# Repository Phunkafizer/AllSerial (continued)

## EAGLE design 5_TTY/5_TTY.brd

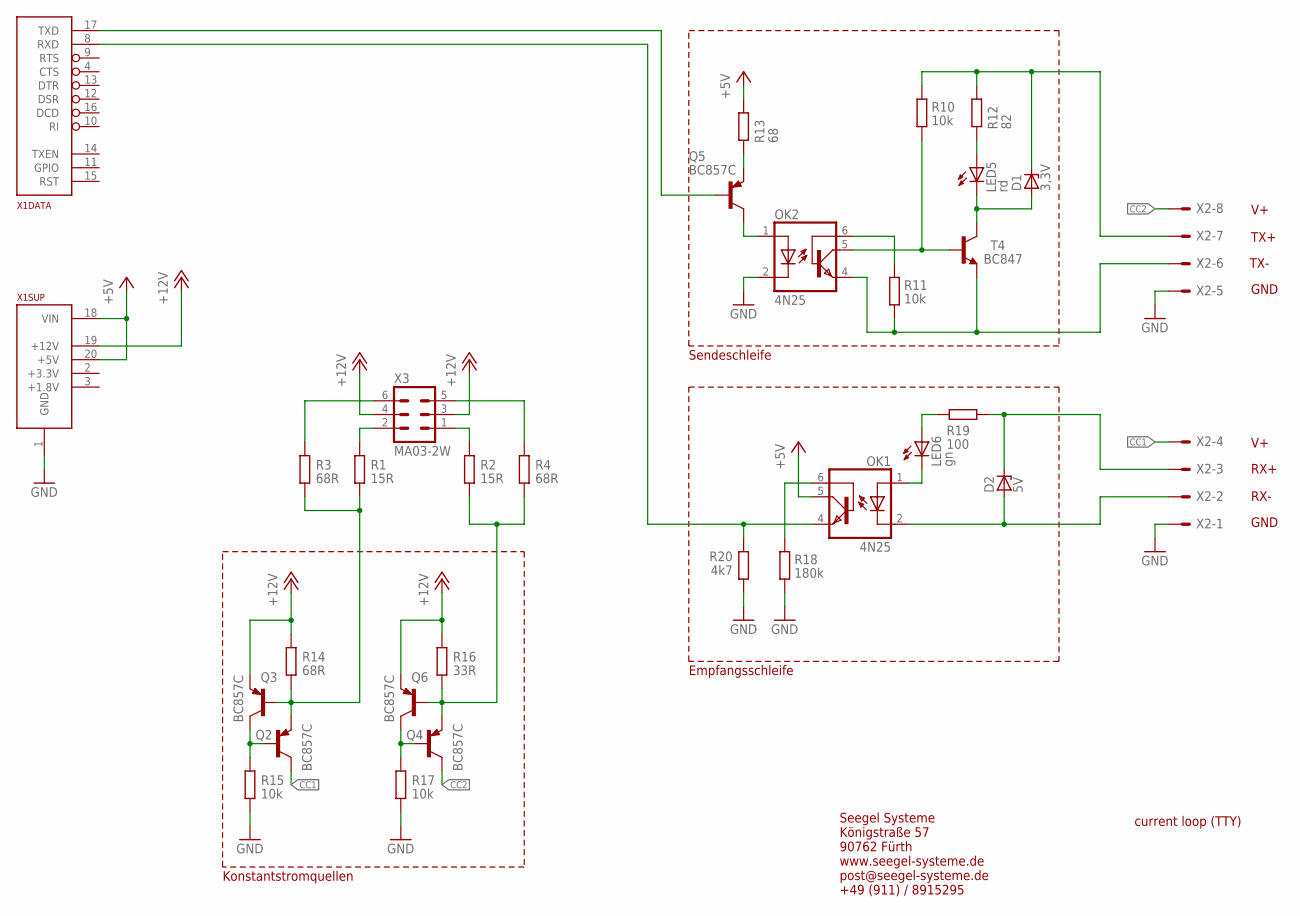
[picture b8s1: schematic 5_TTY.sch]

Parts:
D1: 3,3V; SOT23
D2: 5V; SOT23
LED5: rd; CHIPLED_0603
LED6: gn; CHIPLED_0603
OK1, OK2: 4N25; DIL06; FARNELL 1612454
Q2, Q3, Q4, Q5, Q6: BC857C; SOT23-BEC; FARNELL 8734771
R1, R2: 15R; R0805; FARNELL 2498090
R3, R4, R14: 68R; R0805; FARNELL 2498090
R10, R11: 10k; R0805; FARNELL 2498051
R12: 82; R0805; FARNELL 2498057
R13: 68; R0805; FARNELL 2498057
R15, R17: 10k; R0805; FARNELL 2502672
R16: 33R; R0805; FARNELL 2498090
R18: 180k; R0805; FARNELL 2498051
R19: 100; R0805; FARNELL 2498057
R20: 4k7; R0805; FARNELL 2498050
T4: BC847; SOT23; FARNELL 1081230
X1: ALLSERIALSLAVE; DAUGHTER-THT
X2: AKL18X-08W; AKL182-08
X3: MA03-2W

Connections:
+5V: OK1.5 (COL), R13.1, X1.18 (VIN), X1.20 (+5V)
+12V: Q3.E, Q6.E, R14.1, R16.1, X1.19 (+12V), X3.3, X3.4
CC1: Q2.C, X2.P$4
CC2: Q4.C, X2.P$8
GND: OK2.2 (C), R15.1, R17.1, R18.2, R20.1, X1.1 (GND), X2.P$1, X2.P$5
unnamed: OK1.6 (BAS), R18.1
unnamed: R1.1, X3.2
unnamed: R2.1, X3.1
unnamed: OK2.4 (EMI), R11.2, T4.2 (E), X2.P$6
unnamed: R3.1, X3.6
unnamed: R4.1, X3.5
unnamed: D2.3 (C), R19.1, X2.P$3
unnamed: D2.1 (A), OK1.2 (C), X2.P$2
unnamed: Q4.B, Q6.C, R17.2
unnamed: OK1.4 (EMI), R20.2, X1.8 (RXD)
unnamed: Q4.E, Q6.B, R2.2, R4.2, R16.2
unnamed: OK2.6 (BAS), R11.1
unnamed: OK2.5 (COL), R10.2, T4.1 (B)
unnamed: D1.1 (A), LED5.C, T4.3 (C)
unnamed: Q2.B, Q3.C, R15.2
unnamed: LED5.A, R12.2
unnamed: Q2.E, Q3.B, R1.2, R3.2, R14.2
unnamed: OK2.1 (A), Q5.C
unnamed: Q5.E, R13.2
unnamed: LED6.C, OK1.1 (A)
unnamed: LED6.A, R19.2
unnamed: Q5.B, X1.17 (TXD)
TXP: D1.3 (C), R10.1, R12.1, X2.P$7

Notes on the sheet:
current loop (TTY)
Konstantstromquellen
Empfangsschleife
Sendeschleife
Seegel Systeme Königstraße 57 90762 Fürth www.seegel-systeme.de post@seegel-systeme.de +49 (911) / 8915295
TX+
TX-
GND
RX+
RX-

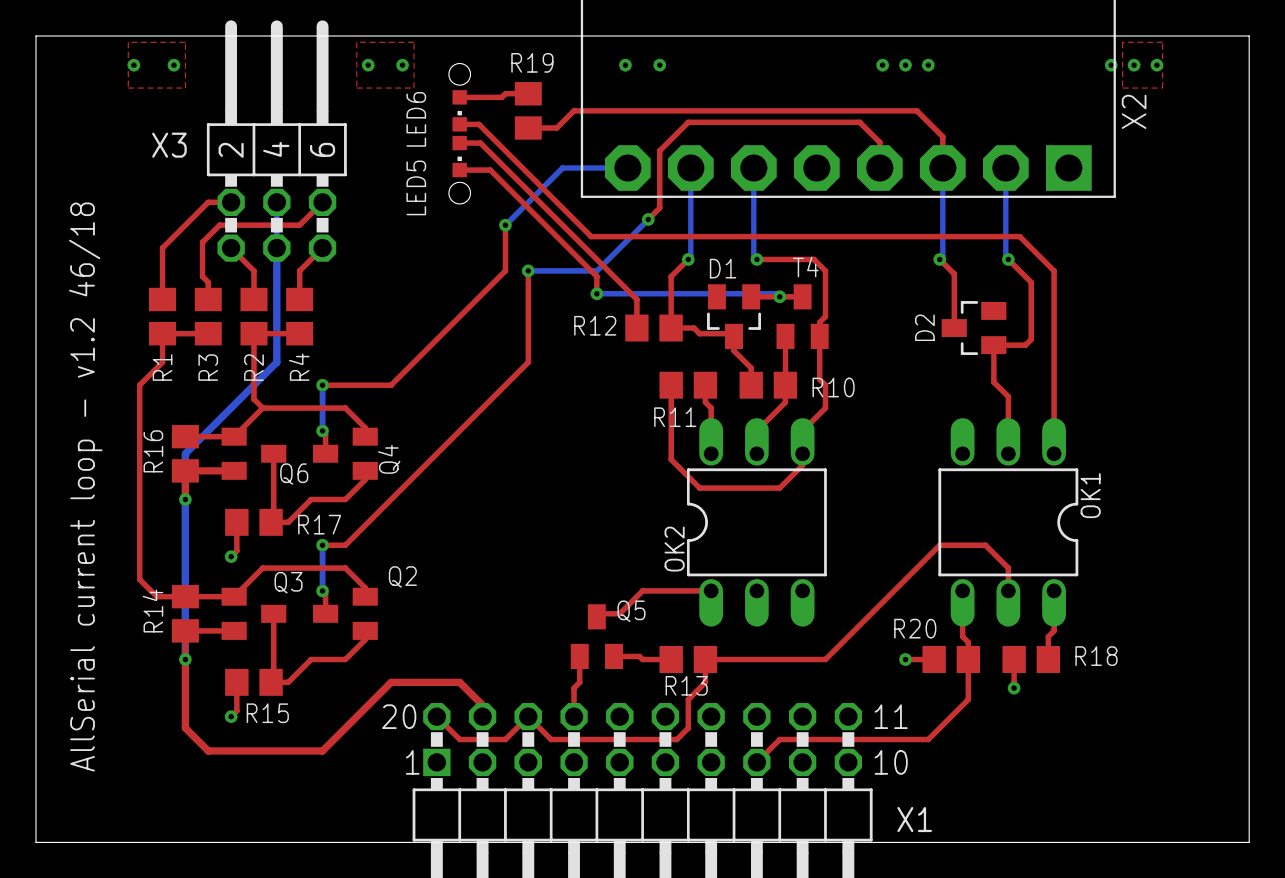
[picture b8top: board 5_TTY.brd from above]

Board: 2 copper layers, 67.4 x 44.8 mm, 31 parts (0 on the bottom side), 28 nets.

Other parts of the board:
U$7: 1296.2012

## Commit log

2018-07-07 add mainboard front panel image
2018-07-07 adding schematic & images
2018-07-07 update images
2018-07-07 imagetest
2018-07-07 remove imagetests
2018-07-07 Corrected RST pin
2018-07-07 RS232 routing
2018-07-07 board seperation
2018-07-07 update lib
2018-07-08 Improve lib
    Route RS232 board
    Route TTL board
2018-07-10 Add USB pins
2018-07-10 finish LIN schematic
2018-07-12 update lib
    restructured
2018-07-12 correct paths
2018-07-12 added mBus master
2018-07-12 updated readme & mainboard
2018-07-12 insert diode for supply
2018-07-17 Add 2mm front line
2018-07-17 finish FTDI PCB
2018-07-17 finish RS485 PCB
2018-07-17 fix connector for LA
2018-07-18 Add ESD protection
2018-07-18 Add BOM
2018-07-18 add and correct BOMs
2018-07-20 new BOMs,
    finish TTY board
2018-07-20 add schematics
2018-07-25 Clean up
2018-07-25 renaming, add front
2018-07-25 add front
2018-07-25 change diodes
2018-07-31 add author
2018-09-01 change to libv2
2018-09-01 update graphics
2018-09-21 new lib, change pinout!
2018-09-26 final design & order
2018-09-26 use new lib
2018-09-26 fix measure layer
2018-10-01 Update BOM & pics
2018-10-01 Add order codes
2018-10-01 update BOM
2018-10-03 fix BOM for MAX211
2018-10-07 add eagle front boards
2018-10-07 cleanup
2018-10-07 fix GND connection
2018-10-07 update boms
2018-10-09 renaming
2018-10-09 update bills of material
2018-10-09 Add front, update png, clean up
2018-10-09 update png & cleanup
2018-10-09 fix link
2018-10-09 fix dir
2018-10-09 fix image link
2018-10-12 BOM updates
2018-10-15 correct connector labels
2018-10-15 smaller images
2018-10-15 image resize
2018-10-22 more readme
2018-10-22 more readme & pics
2018-10-22 rename pic
2018-10-22 correct link
2018-10-23 Update PDF
2018-10-23 add pdf docs
    add gerber data
    cleanup
    renaming
2018-10-23 layout
2018-10-23 Create LICENSE
2018-10-30 added 10 arduino module
2018-10-30 add 1wire files
2018-10-30 add front boards
2018-11-03 adding 1wire and eBus boards
2018-11-03 add ESP & arduino board
2018-11-03 Update Link
2018-11-19 pro mini layout corrected
2018-11-19 Revert "pro mini layout corrected"
    This reverts commit e6acf7b114fc184efa746b3a51c54623d1353390.
2018-11-19 Use lib elements
2018-11-19 Cleanup, front with lib elements
2018-11-19 Revert "Cleanup, front with lib elements"
    This reverts commit d2aae2c670d4479654c143ea750e88e2046a00ae.
2018-11-19 Cleanup, front lib elements
2018-11-19 cleanup & update docu
2024-07-19 Truncated hist
2024-07-19 Added new boards
2024-07-19 add WiFi Master Front
    add symbol lib for fronts
2024-07-19 Update AllSerial libraries
    update projects
    add slave project template
2024-07-19 Migrate to new KiCad Version
    Add SMA connector front
2024-07-19 Update TTY CL slave board
    Add ESP32 S3 WiFi MasterBoard
    Update libs
2024-07-19 add images
    update readme
2024-07-23 improve board/front links
    clean up
2025-07-08 Migrate to KiCad 9
    Add eBus board
    Add various libraries
2025-07-09 improve AllSerial library
    add assets for README
    update README
    cleanup
2025-07-09 add frontpanel STEP files
2025-07-16 Improve libraries
2025-07-20 Remove pads from cutouts
2025-08-07 FTDI master: Change footprint of isolators
    minor improvments
2025-08-21 Add python testskript
    Add mainboard tester
    Add libraries
2025-08-21 add wiring schemes
